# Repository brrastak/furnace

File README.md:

# Furnace for glass fusing

Glass fusing - joining of the pieces of glass. Glass isn't really melted, but is softer than in the normal condition. Planned furnace maximum temperature - 900 °C. Unfortunetely, the project was cancelled due to political reasons. I just want to close my gestalt and finish at least PCBs and firmware.

TODO: more detailed description.

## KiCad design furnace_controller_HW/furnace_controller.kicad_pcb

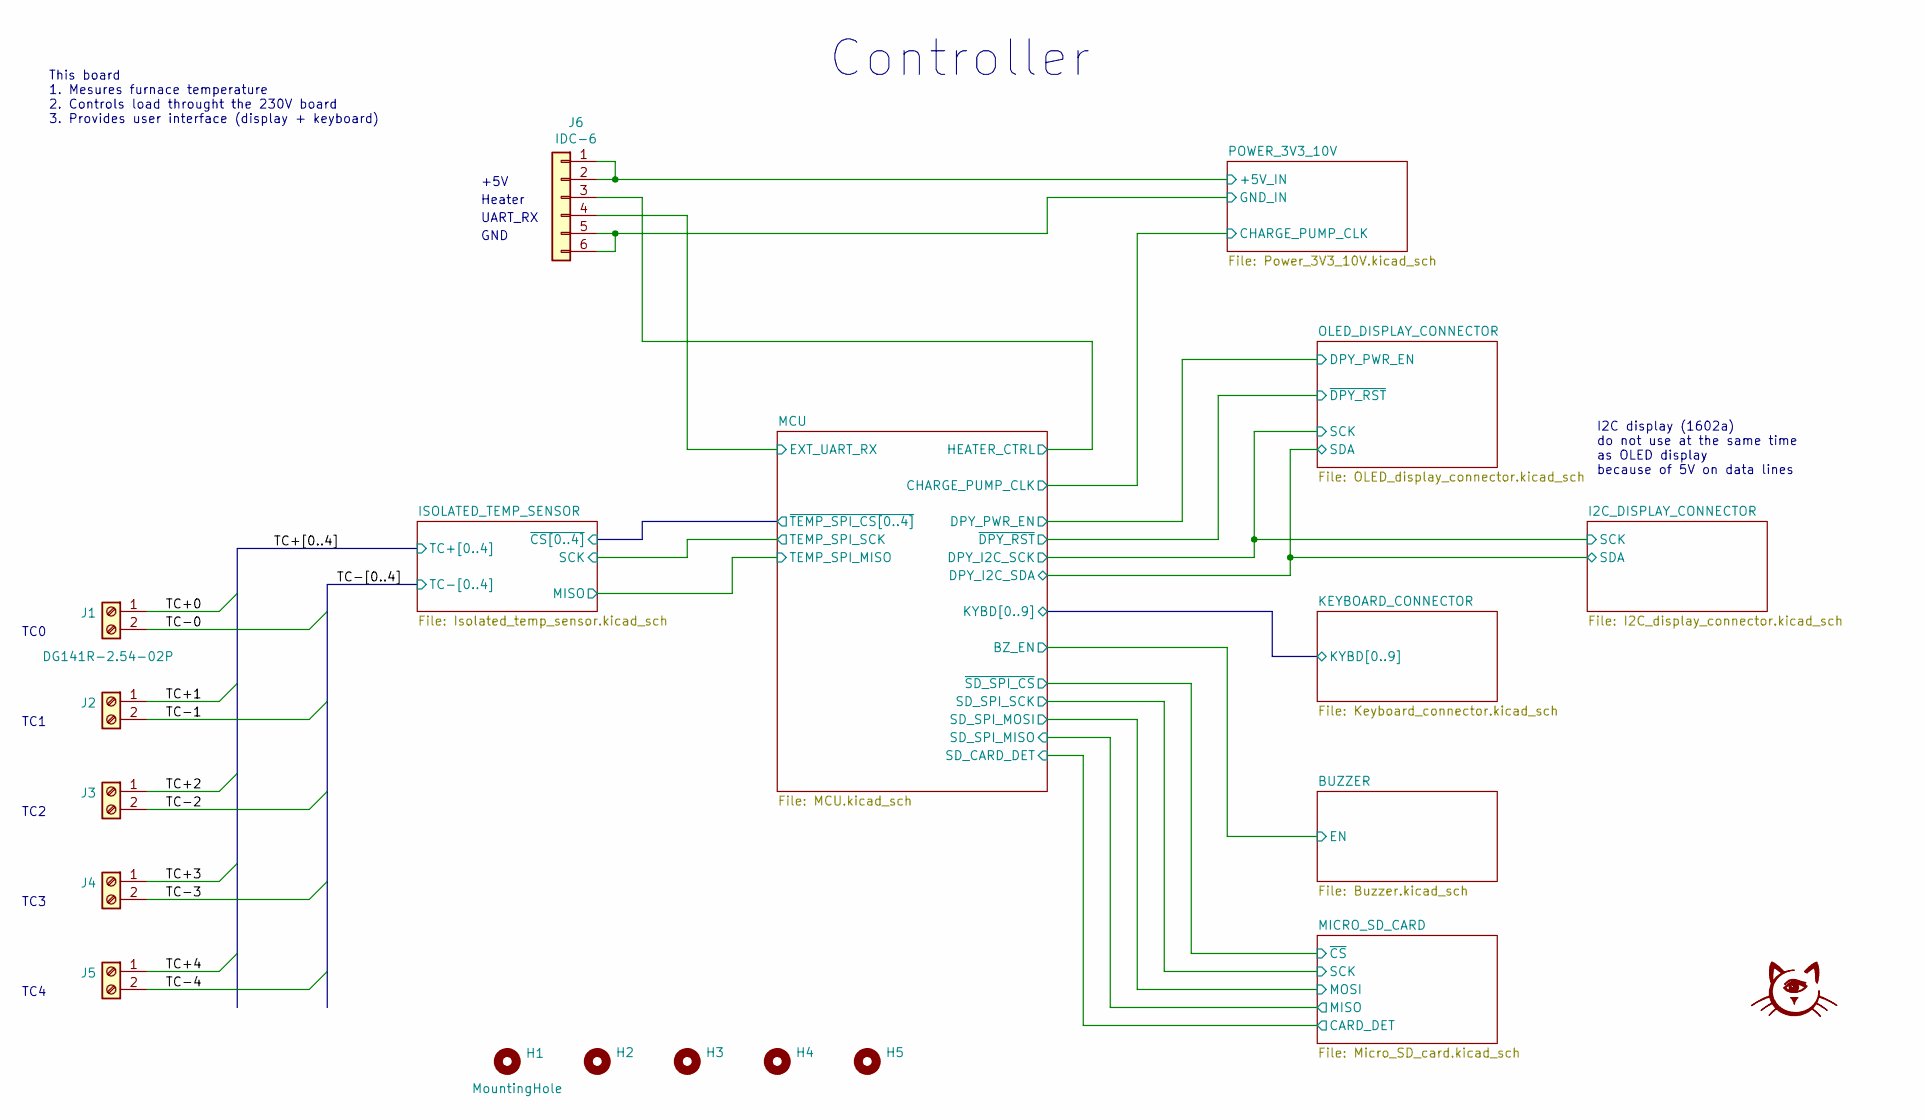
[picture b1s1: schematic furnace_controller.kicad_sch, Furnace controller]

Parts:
G1: LOGO; stamp
H1, H2, H3, H4, H5: MountingHole; hole_D3.5mm
J1, J2, J3, J4, J5: DG141R-2.54-02P
J6: IDC-6; IDC-Header_2x03_P2.54mm_Vertical

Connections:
/MCU/EXT_UART_RX: J6.4; also elsewhere on the board
/MCU/HEATER_CTRL: J6.3; also elsewhere on the board
/POWER_3V3_10V/+5V_IN: J6.1, J6.2; also elsewhere on the board
/TC+0: J1.1; also elsewhere on the board
/TC+1: J2.1; also elsewhere on the board
/TC+2: J3.1; also elsewhere on the board
/TC+3: J4.1; also elsewhere on the board
/TC+4: J5.1; also elsewhere on the board
/TC-0: J1.2; also elsewhere on the board
/TC-1: J2.2; also elsewhere on the board
/TC-2: J3.2; also elsewhere on the board
/TC-3: J4.2; also elsewhere on the board
/TC-4: J5.2; also elsewhere on the board
GND: J6.5, J6.6; also elsewhere on the board

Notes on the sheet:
Controller
TC0
UART_RX
GND
+5V
I2C display (1602a) do not use at the same time as OLED display because of 5V on data lines
TC2
TC1
TC4
TC3
This board 1. Mesures furnace temperature 2. Controls load throught the 230V board 3. Provides user interface (display + keyboard)
Heater

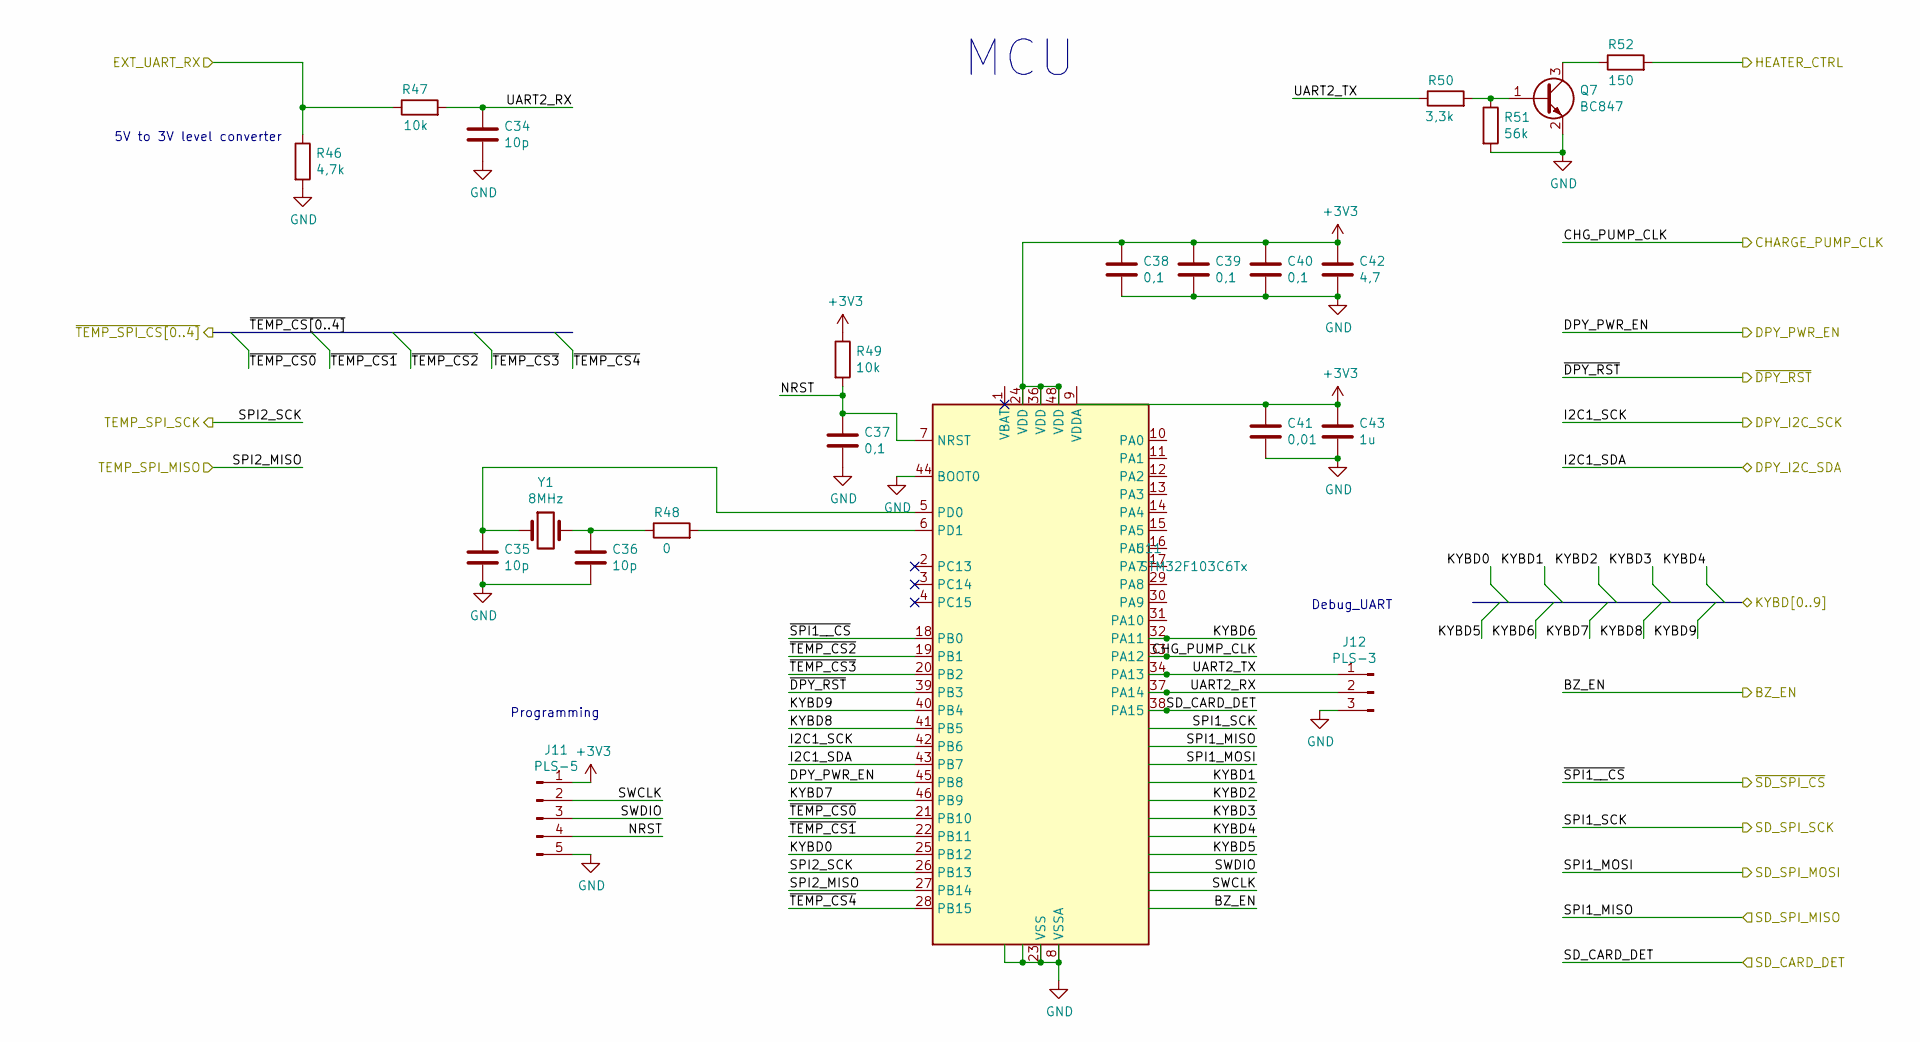
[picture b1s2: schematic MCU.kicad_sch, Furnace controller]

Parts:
C34, C35, C36: 10p; C_0603_1608Metric_Pad1.08x0.95mm_HandSolder
C37, C38, C39, C40: 0,1; C_0603_1608Metric_Pad1.08x0.95mm_HandSolder
C41: 0,01; C_0603_1608Metric_Pad1.08x0.95mm_HandSolder
C42: 4,7; C_1206_3216Metric_Pad1.33x1.80mm_HandSolder
C43: 1u; C_0603_1608Metric_Pad1.08x0.95mm_HandSolder
J11: PLS-5; PinHeader_1x05_P2.54mm_Vertical
J12: PLS-3; PinHeader_1x03_P2.54mm_Vertical
Q7: BC847; SOT-23
R46: 4,7k; R_0603_1608Metric_Pad0.98x0.95mm_HandSolder
R47, R49: 10k; R_0603_1608Metric_Pad0.98x0.95mm_HandSolder
R48: 0; R_0603_1608Metric_Pad0.98x0.95mm_HandSolder
R50: 3,3k; R_0603_1608Metric_Pad0.98x0.95mm_HandSolder
R51: 56k; R_0603_1608Metric_Pad0.98x0.95mm_HandSolder
R52: 150; R_0603_1608Metric_Pad0.98x0.95mm_HandSolder
U11: STM32F103C6Tx; LQFP-48_7x7mm_P0.5mm
Y1: 8MHz; Crystal_SMD_HC49-SD

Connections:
+3V3: C38.1, C39.1, C40.1, C41.1, C42.1, C43.1, J11.1, R49.1, U11.9 (VDDA), U11.24 (VDD), U11.36 (VDD), U11.48 (VDD); also elsewhere on the board
/ISOLATED_TEMP_SENSOR/MISO: U11.27 (PB14); also elsewhere on the board
/ISOLATED_TEMP_SENSOR/SCK: U11.26 (PB13); also elsewhere on the board
/ISOLATED_TEMP_SENSOR/~CS0: U11.21 (PB10); also elsewhere on the board
/ISOLATED_TEMP_SENSOR/~CS1: U11.22 (PB11); also elsewhere on the board
/ISOLATED_TEMP_SENSOR/~CS2: U11.19 (PB1); also elsewhere on the board
/ISOLATED_TEMP_SENSOR/~CS3: U11.20 (PB2); also elsewhere on the board
/ISOLATED_TEMP_SENSOR/~CS4: U11.28 (PB15); also elsewhere on the board
/KEYBOARD_CONNECTOR/KYBD0: U11.25 (PB12); also elsewhere on the board
/KEYBOARD_CONNECTOR/KYBD1: U11.29 (PA8); also elsewhere on the board
/KEYBOARD_CONNECTOR/KYBD2: U11.30 (PA9); also elsewhere on the board
/KEYBOARD_CONNECTOR/KYBD3: U11.31 (PA10); also elsewhere on the board
/KEYBOARD_CONNECTOR/KYBD4: U11.32 (PA11); also elsewhere on the board
/KEYBOARD_CONNECTOR/KYBD5: U11.33 (PA12); also elsewhere on the board
/KEYBOARD_CONNECTOR/KYBD6: U11.10 (PA0); also elsewhere on the board
/KEYBOARD_CONNECTOR/KYBD7: U11.46 (PB9); also elsewhere on the board
/KEYBOARD_CONNECTOR/KYBD8: U11.41 (PB5); also elsewhere on the board
/KEYBOARD_CONNECTOR/KYBD9: U11.40 (PB4); also elsewhere on the board
/MCU/BZ_EN: U11.38 (PA15); also elsewhere on the board
/MCU/CHARGE_PUMP_CLK: U11.11 (PA1); also elsewhere on the board
/MCU/DPY_I2C_SCK: U11.42 (PB6); also elsewhere on the board
/MCU/DPY_I2C_SDA: U11.43 (PB7); also elsewhere on the board
/MCU/DPY_PWR_EN: U11.45 (PB8); also elsewhere on the board
/MCU/EXT_UART_RX: R46.1, R47.1; also elsewhere on the board
/MCU/HEATER_CTRL: R52.2; also elsewhere on the board
/MCU/NRST: C37.1, J11.4, R49.2, U11.7 (NRST)
/MCU/~DPY_RST: U11.39 (PB3); also elsewhere on the board
/MICRO_SD_CARD/CARD_DET: U11.14 (PA4); also elsewhere on the board
/MICRO_SD_CARD/MISO: U11.16 (PA6); also elsewhere on the board
/MICRO_SD_CARD/MOSI: U11.17 (PA7); also elsewhere on the board
/MICRO_SD_CARD/SCK: U11.15 (PA5); also elsewhere on the board
/MICRO_SD_CARD/~CS: U11.18 (PB0); also elsewhere on the board
GND: C34.2, C35.2, C36.2, C37.2, C38.2, C39.2, C40.2, C41.2, C42.2, C43.2, J11.5, J12.3, Q7.2 (E), R46.2, R51.2, U11.8 (VSSA), U11.23 (VSS), U11.35 (VSS), U11.44 (BOOT0), U11.47 (VSS); also elsewhere on the board
unnamed: C35.1, U11.5 (PD0), Y1.1
unnamed: C36.1, R48.1, Y1.2
unnamed: Q7.1 (B), R50.2, R51.1
unnamed: Q7.3 (C), R52.1
unnamed: R48.2, U11.6 (PD1)

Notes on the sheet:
Debug_UART
Programming
MCU
5V to 3V level converter

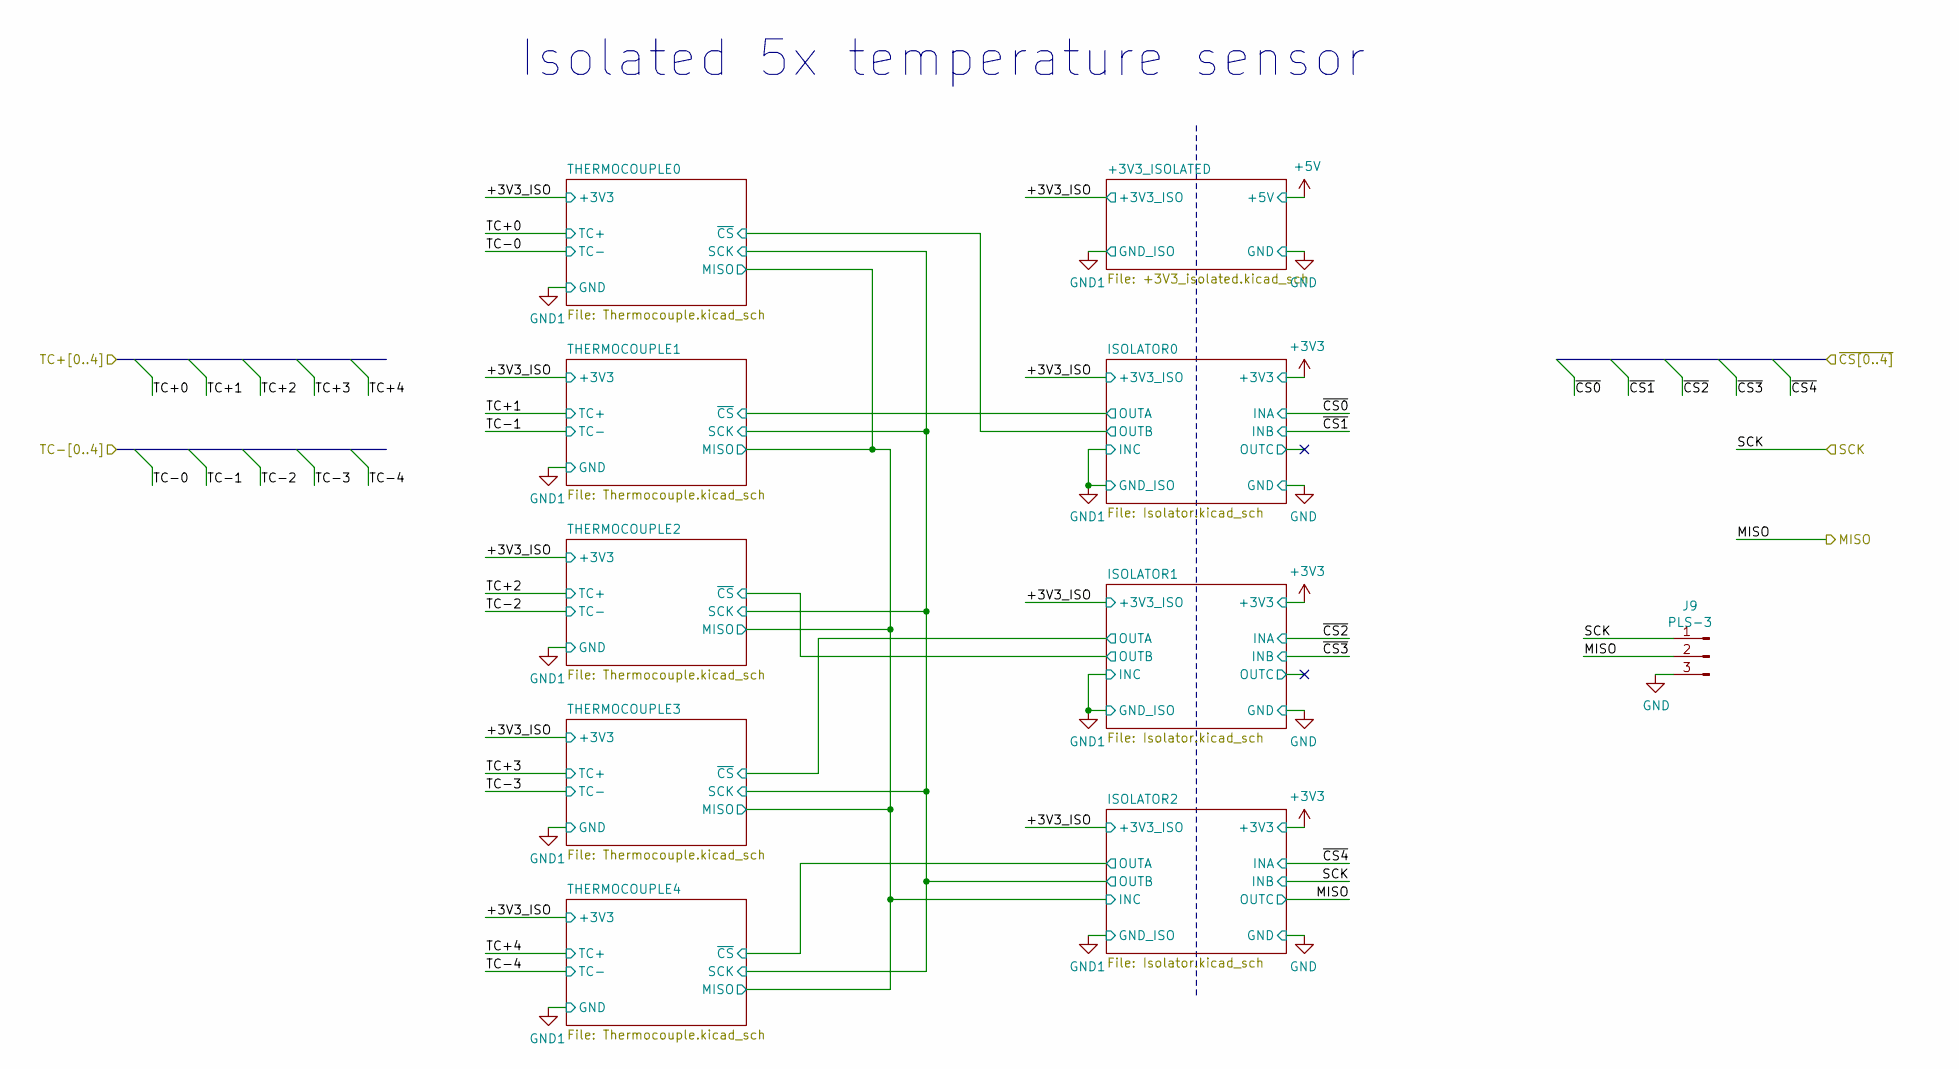
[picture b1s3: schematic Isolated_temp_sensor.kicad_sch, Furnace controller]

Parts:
J9: PLS-3; PinHeader_1x03_P2.54mm_Vertical

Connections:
/ISOLATED_TEMP_SENSOR/MISO: J9.2; also elsewhere on the board
/ISOLATED_TEMP_SENSOR/SCK: J9.1; also elsewhere on the board
GND: J9.3; also elsewhere on the board

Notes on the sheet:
Isolated 5x temperature sensor

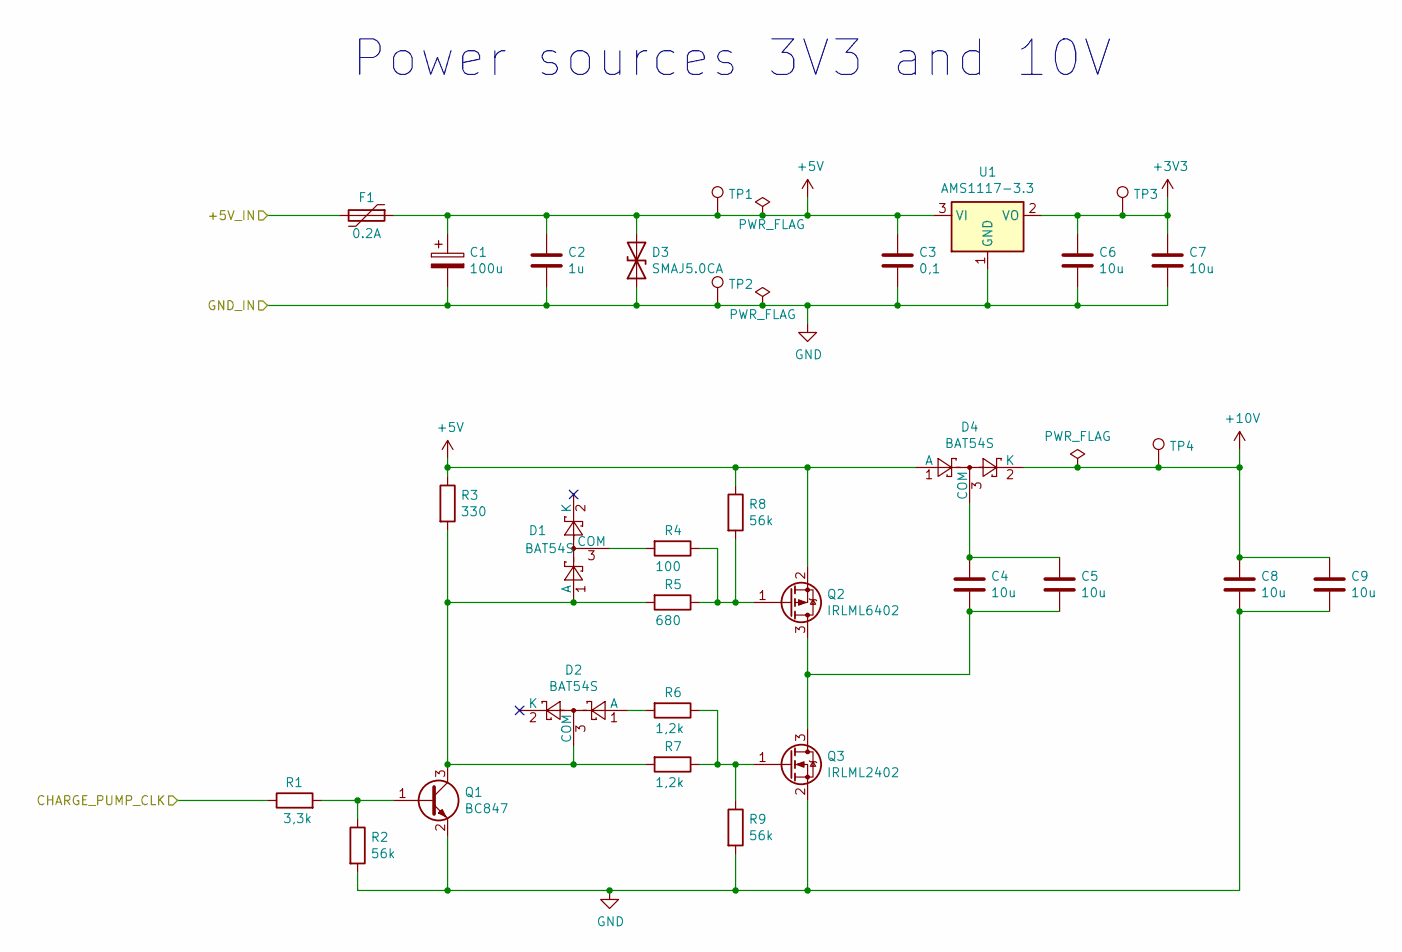
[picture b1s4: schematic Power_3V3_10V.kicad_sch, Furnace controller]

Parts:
C1: 100u; CP_Radial_D5.0mm_P2.00mm
C2: 1u; C_0603_1608Metric_Pad1.08x0.95mm_HandSolder
C3: 0,1; C_0603_1608Metric_Pad1.08x0.95mm_HandSolder
C4, C5, C6, C7, C8, C9: 10u; C_1206_3216Metric_Pad1.33x1.80mm_HandSolder
D1, D2, D4: BAT54S; SOT-23
D3: SMAJ5.0CA; D_SMB_Handsoldering
F1: 0.2A; Fuse_1206_3216Metric_Pad1.42x1.75mm_HandSolder
Q1: BC847; SOT-23
Q2: IRLML6402; SOT-23
Q3: IRLML2402; SOT-23
R1: 3,3k; R_0603_1608Metric_Pad0.98x0.95mm_HandSolder
R2, R8, R9: 56k; R_0603_1608Metric_Pad0.98x0.95mm_HandSolder
R3: 330; R_0603_1608Metric_Pad0.98x0.95mm_HandSolder
R4: 100; R_0603_1608Metric_Pad0.98x0.95mm_HandSolder
R5: 680; R_0603_1608Metric_Pad0.98x0.95mm_HandSolder
R6, R7: 1,2k; R_0603_1608Metric_Pad0.98x0.95mm_HandSolder
TP1, TP2, TP3, TP4: TestPoint; TP
U1: AMS1117-3.3; SOT-223-3_TabPin2

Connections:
+3V3: C6.1, C7.1, TP3.1, U1.2 (VO); also elsewhere on the board
+5V: C1.1, C2.1, C3.1, D3.2 (A2), D4.1 (A), F1.1, Q2.2 (S), R3.1, R8.1, TP1.1, U1.3 (VI); also elsewhere on the board
+10V: C8.1, C9.1, D4.2 (K), TP4.1; also elsewhere on the board
/MCU/CHARGE_PUMP_CLK: R1.1; also elsewhere on the board
/POWER_3V3_10V/+5V_IN: F1.2; also elsewhere on the board
GND: C1.2, C2.2, C3.2, C6.2, C7.2, C8.2, C9.2, D3.1 (A1), Q1.2 (E), Q3.2 (S), R2.2, R9.2, TP2.1, U1.1 (GND); also elsewhere on the board
unnamed: C4.1, C5.1, D4.3 (COM)
unnamed: C4.2, C5.2, Q2.3 (D), Q3.3 (D)
unnamed: D1.1 (A), D2.3 (COM), Q1.3 (C), R3.2, R5.2, R7.2
unnamed: D1.3 (COM), R4.2
unnamed: D2.1 (A), R6.2
unnamed: Q1.1 (B), R1.2, R2.1
unnamed: Q2.1 (G), R4.1, R5.1, R8.2
unnamed: Q3.1 (G), R6.1, R7.1, R9.1

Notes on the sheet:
Power sources 3V3 and 10V

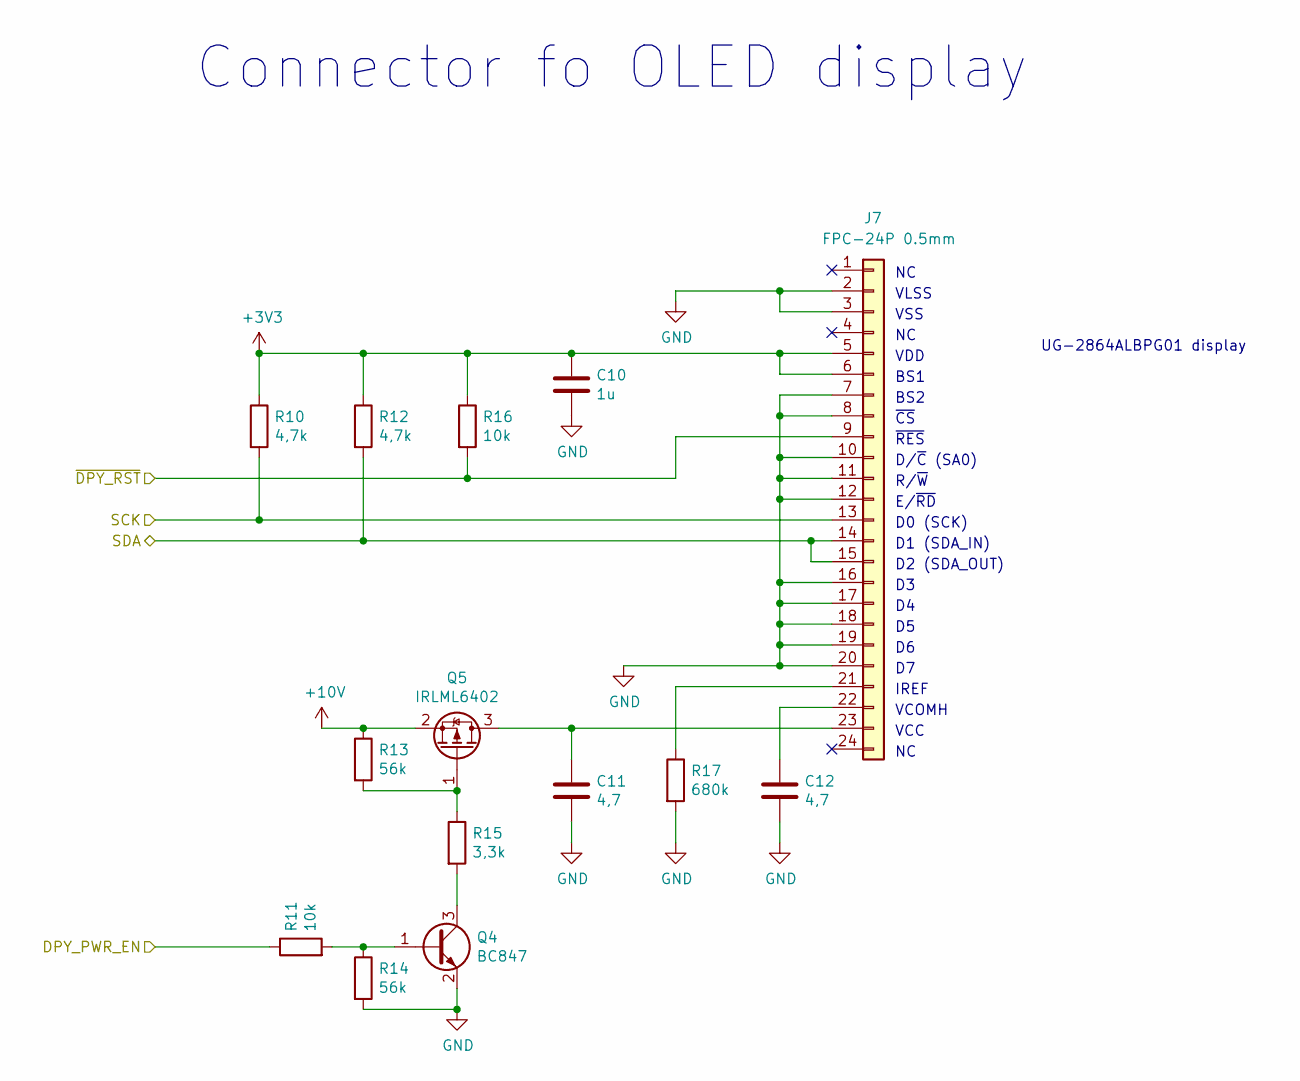
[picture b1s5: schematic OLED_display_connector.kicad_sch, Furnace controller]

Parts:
C10: 1u; C_0603_1608Metric_Pad1.08x0.95mm_HandSolder
C11, C12: 4,7; C_1206_3216Metric_Pad1.33x1.80mm_HandSolder
J7: FPC-24P 0.5mm; Hirose_FH12-24S-0.5SH_1x24-1MP_P0.50mm_Horizontal
Q4: BC847; SOT-23
Q5: IRLML6402; SOT-23
R10, R12: 4,7k; R_0603_1608Metric_Pad0.98x0.95mm_HandSolder
R11, R16: 10k; R_0603_1608Metric_Pad0.98x0.95mm_HandSolder
R13, R14: 56k; R_0603_1608Metric_Pad0.98x0.95mm_HandSolder
R15: 3,3k; R_0603_1608Metric_Pad0.98x0.95mm_HandSolder
R17: 680k; R_0603_1608Metric_Pad0.98x0.95mm_HandSolder

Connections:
+3V3: C10.1, J7.5, J7.6, R10.1, R12.1, R16.1; also elsewhere on the board
+10V: Q5.2 (S), R13.1; also elsewhere on the board
/MCU/DPY_I2C_SCK: J7.13, R10.2; also elsewhere on the board
/MCU/DPY_I2C_SDA: J7.14, J7.15, R12.2; also elsewhere on the board
/MCU/DPY_PWR_EN: R11.1; also elsewhere on the board
/MCU/~DPY_RST: J7.9, R16.2; also elsewhere on the board
GND: C10.2, C11.2, C12.2, J7.2, J7.3, J7.7, J7.8, J7.10, J7.11, J7.12, J7.16, J7.17, J7.18, J7.19, J7.20, Q4.2 (E), R14.2, R17.2; also elsewhere on the board
unnamed: C11.1, J7.23, Q5.3 (D)
unnamed: C12.1, J7.22
unnamed: J7.21, R17.1
unnamed: Q4.1 (B), R11.2, R14.1
unnamed: Q4.3 (C), R15.2
unnamed: Q5.1 (G), R13.2, R15.1

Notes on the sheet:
BS1
BS2
VLSS
UG-2864ALBPG01 display
R/~{W}
~{RES}
VSS
Connector fo OLED display
VCOMH
E/~{RD}
D/~{C} (SA0)
D1 (SDA_IN)
VCC
IREF
~{CS}
D0 (SCK)
D2 (SDA_OUT)
VDD

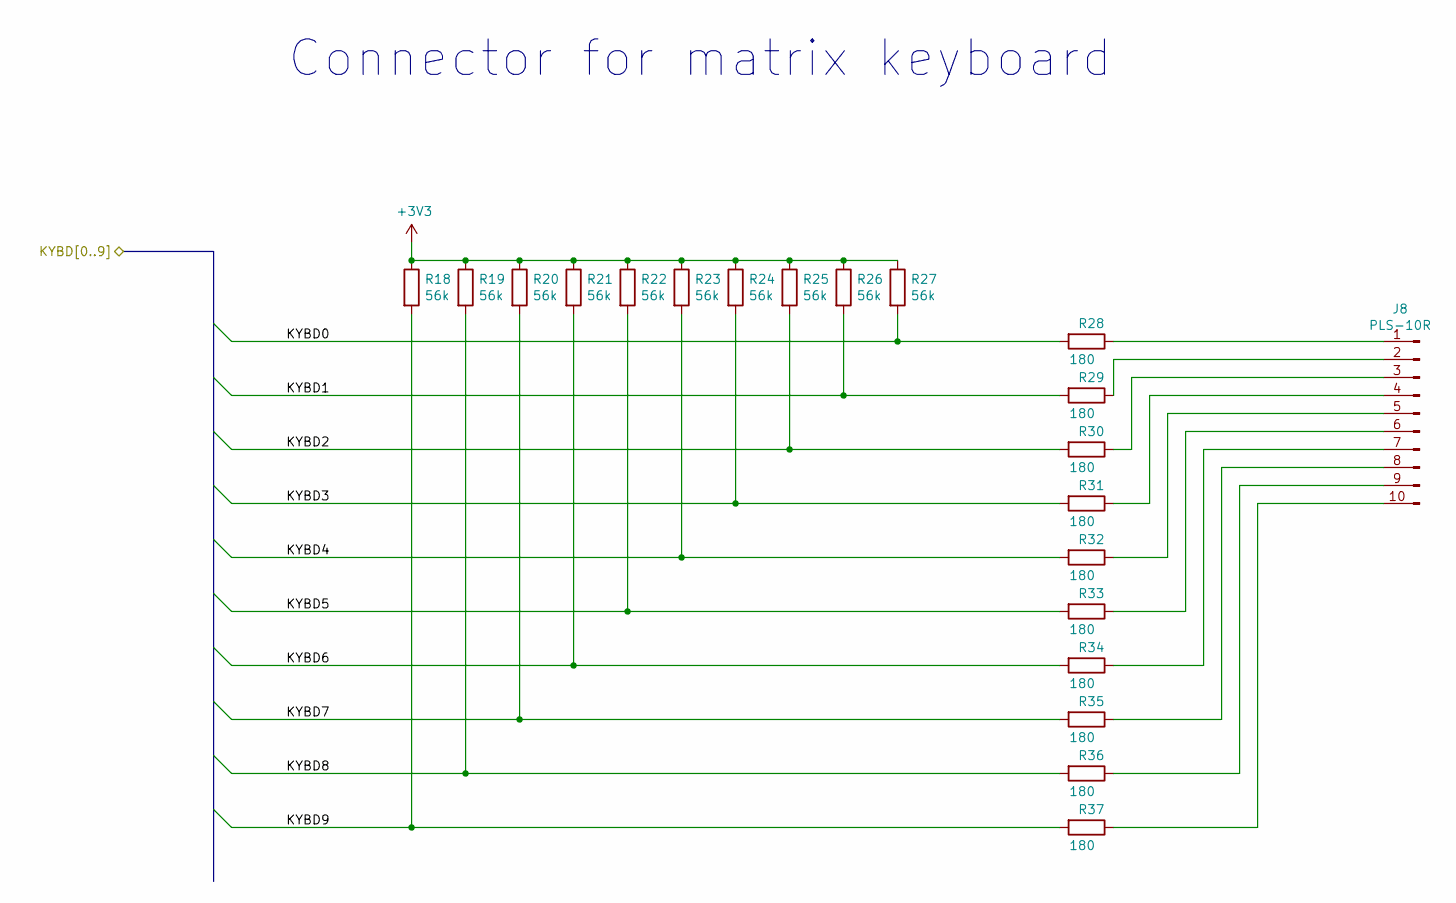
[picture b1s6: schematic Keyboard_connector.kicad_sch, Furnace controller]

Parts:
J8: PLS-10R; PinHeader_1x10_P2.54mm_Vertical
R18, R19, R20, R21, R22, R23, R24, R25, R26, R27: 56k; R_0603_1608Metric_Pad0.98x0.95mm_HandSolder
R28, R29, R30, R31, R32, R33, R34, R35, R36, R37: 180; R_0603_1608Metric_Pad0.98x0.95mm_HandSolder

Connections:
+3V3: R18.1, R19.1, R20.1, R21.1, R22.1, R23.1, R24.1, R25.1, R26.1, R27.1; also elsewhere on the board
/KEYBOARD_CONNECTOR/KYBD0: R27.2, R28.2; also elsewhere on the board
/KEYBOARD_CONNECTOR/KYBD1: R26.2, R29.2; also elsewhere on the board
/KEYBOARD_CONNECTOR/KYBD2: R25.2, R30.2; also elsewhere on the board
/KEYBOARD_CONNECTOR/KYBD3: R24.2, R31.2; also elsewhere on the board
/KEYBOARD_CONNECTOR/KYBD4: R23.2, R32.2; also elsewhere on the board
/KEYBOARD_CONNECTOR/KYBD5: R22.2, R33.2; also elsewhere on the board
/KEYBOARD_CONNECTOR/KYBD6: R21.2, R34.2; also elsewhere on the board
/KEYBOARD_CONNECTOR/KYBD7: R20.2, R35.2; also elsewhere on the board
/KEYBOARD_CONNECTOR/KYBD8: R19.2, R36.2; also elsewhere on the board
/KEYBOARD_CONNECTOR/KYBD9: R18.2, R37.2; also elsewhere on the board
unnamed: J8.1, R28.1
unnamed: J8.2, R29.1
unnamed: J8.3, R30.1
unnamed: J8.4, R31.1
unnamed: J8.5, R32.1
unnamed: J8.6, R33.1
unnamed: J8.7, R34.1
unnamed: J8.8, R35.1
unnamed: J8.9, R36.1
unnamed: J8.10, R37.1

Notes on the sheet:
Connector for matrix keyboard

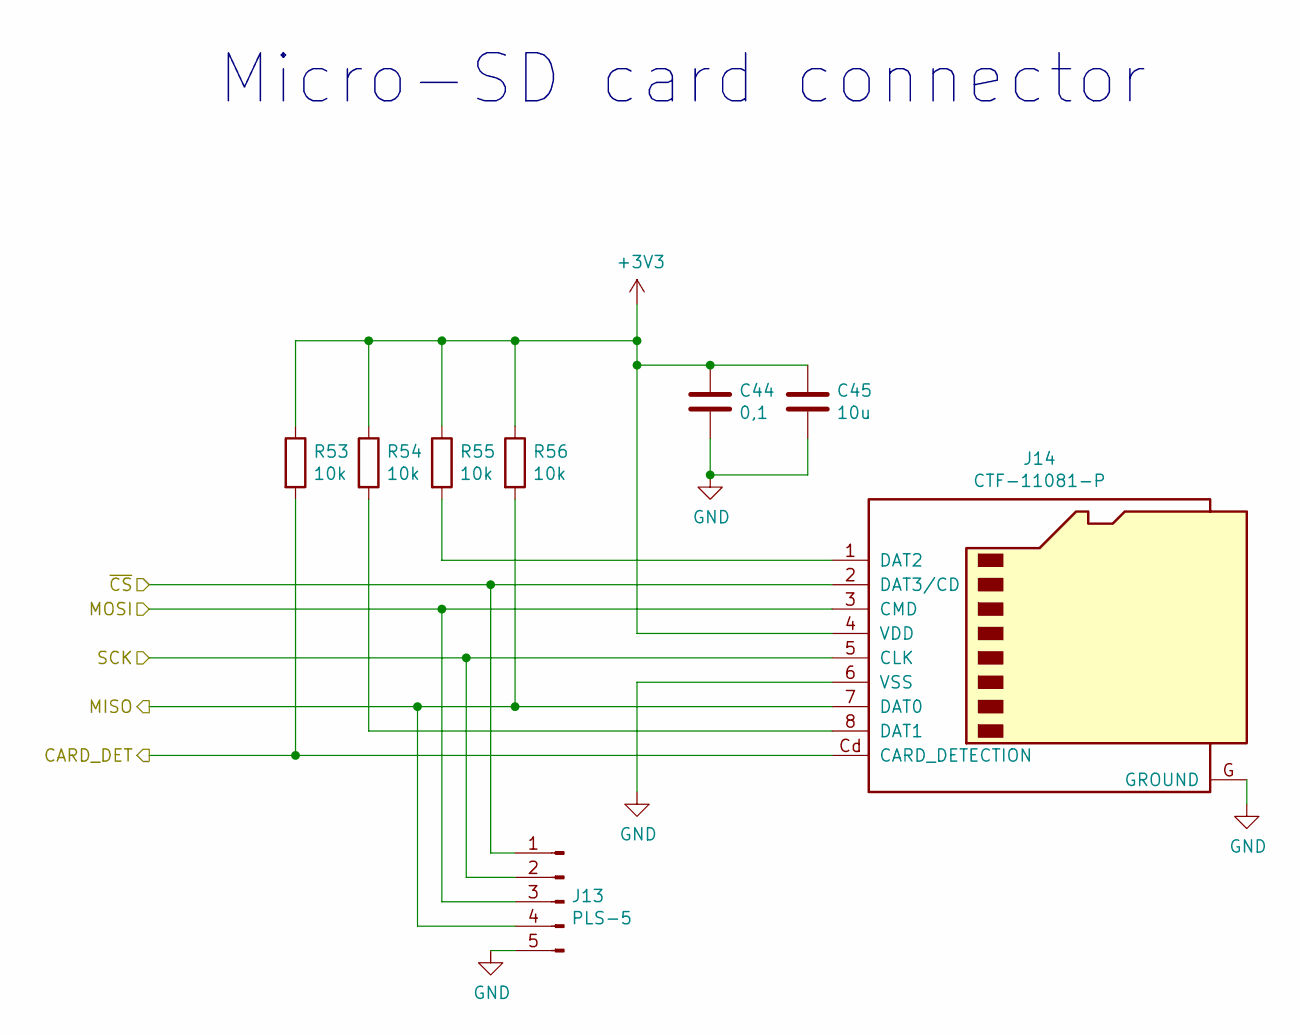
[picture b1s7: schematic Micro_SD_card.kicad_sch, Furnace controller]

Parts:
C44: 0,1; C_0603_1608Metric_Pad1.08x0.95mm_HandSolder
C45: 10u; C_1206_3216Metric_Pad1.33x1.80mm_HandSolder
J13: PLS-5; PinHeader_1x05_P2.54mm_Vertical
J14: CTF-11081-P
R53, R54, R55, R56: 10k; R_0603_1608Metric_Pad0.98x0.95mm_HandSolder

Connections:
+3V3: C44.1, C45.1, J14.4 (VDD), R53.1, R54.1, R55.1, R56.1; also elsewhere on the board
/MICRO_SD_CARD/CARD_DET: J14.Cd (CARD_DETECTION), R53.2; also elsewhere on the board
/MICRO_SD_CARD/MISO: J13.4, J14.7 (DAT0), R56.2; also elsewhere on the board
/MICRO_SD_CARD/MOSI: J13.3, J14.3 (CMD); also elsewhere on the board
/MICRO_SD_CARD/SCK: J13.2, J14.5 (CLK); also elsewhere on the board
/MICRO_SD_CARD/~CS: J13.1, J14.2 (DAT3/CD); also elsewhere on the board
GND: C44.2, C45.2, J13.5, J14.6 (VSS), J14.G (GROUND); also elsewhere on the board
unnamed: J14.1 (DAT2), R55.2
unnamed: J14.8 (DAT1), R54.2

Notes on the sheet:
Micro-SD card connector

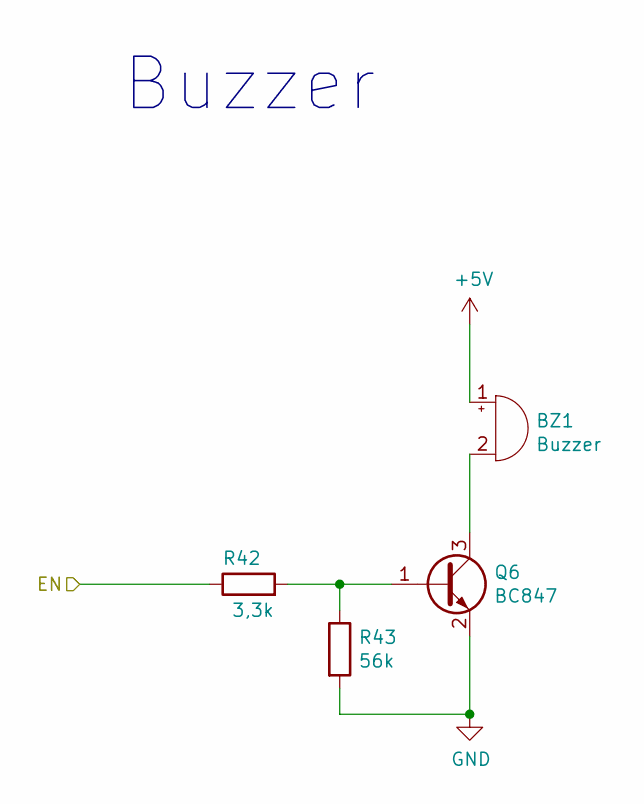
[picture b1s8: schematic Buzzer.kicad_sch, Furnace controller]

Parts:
BZ1: Buzzer; Buzzer_12x9.5RM7.6
Q6: BC847; SOT-23
R42: 3,3k; R_0603_1608Metric_Pad0.98x0.95mm_HandSolder
R43: 56k; R_0603_1608Metric_Pad0.98x0.95mm_HandSolder

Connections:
+5V: BZ1.1 (+); also elsewhere on the board
/MCU/BZ_EN: R42.1; also elsewhere on the board
GND: Q6.2 (E), R43.2; also elsewhere on the board
unnamed: BZ1.2 (-), Q6.3 (C)
unnamed: Q6.1 (B), R42.2, R43.1

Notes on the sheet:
Buzzer

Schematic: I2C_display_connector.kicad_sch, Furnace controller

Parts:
J10: PLS-4R; PinHeader_1x04_P2.54mm_Horizontal
JP1: Jumper_NC_Dual; PinHeader_1x03_P2.54mm_Vertical
R44, R45: 4,7k; R_0603_1608Metric_Pad0.98x0.95mm_HandSolder

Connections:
+3V3: JP1.3; also elsewhere on the board
+5V: JP1.1; also elsewhere on the board
/MCU/DPY_I2C_SCK: J10.1, R44.2; also elsewhere on the board
/MCU/DPY_I2C_SDA: J10.2, R45.2; also elsewhere on the board
GND: J10.4; also elsewhere on the board
unnamed: J10.3, JP1.2, R44.1, R45.1

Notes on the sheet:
I2C display connector for OLED or LCD display

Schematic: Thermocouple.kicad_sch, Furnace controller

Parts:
C13: 0,01; C_0603_1608Metric_Pad1.08x0.95mm_HandSolder
C14: 0,1; C_0603_1608Metric_Pad1.08x0.95mm_HandSolder
U2: MAX31855EASA; SOIC-8_3.9x4.9mm_P1.27mm

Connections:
/ISOLATED_TEMP_SENSOR/+3V3_ISO: C14.1, U2.4 (V_{CC}); also elsewhere on the board
/ISOLATED_TEMP_SENSOR/ISOLATOR0/OUTB: U2.6 (~CS); also elsewhere on the board
/ISOLATED_TEMP_SENSOR/ISOLATOR2/INC: U2.7 (SO); also elsewhere on the board
/ISOLATED_TEMP_SENSOR/ISOLATOR2/OUTB: U2.5 (SCK); also elsewhere on the board
/TC+0: C13.1, U2.3 (T+); also elsewhere on the board
/TC-0: C13.2, U2.2 (T-); also elsewhere on the board
GND1: C14.2, U2.1 (GND); also elsewhere on the board

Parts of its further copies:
C22, C24, C26, C28: 0,01; C_0603_1608Metric_Pad1.08x0.95mm_HandSolder
C23, C25, C27, C29: 0,1; C_0603_1608Metric_Pad1.08x0.95mm_HandSolder
U5, U6, U7, U8: MAX31855EASA; SOIC-8_3.9x4.9mm_P1.27mm

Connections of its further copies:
/ISOLATED_TEMP_SENSOR/+3V3_ISO: C23.1, C25.1, C27.1, C29.1, U5.4 (V_{CC}), U6.4 (V_{CC}), U7.4 (V_{CC}), U8.4 (V_{CC}); also elsewhere on the board
/ISOLATED_TEMP_SENSOR/ISOLATOR0/OUTA: U5.6 (~CS); also elsewhere on the board
/ISOLATED_TEMP_SENSOR/ISOLATOR1/OUTA: U7.6 (~CS); also elsewhere on the board
/ISOLATED_TEMP_SENSOR/ISOLATOR1/OUTB: U6.6 (~CS); also elsewhere on the board
/ISOLATED_TEMP_SENSOR/ISOLATOR2/INC: U5.7 (SO), U6.7 (SO), U7.7 (SO), U8.7 (SO); also elsewhere on the board
/ISOLATED_TEMP_SENSOR/ISOLATOR2/OUTA: U8.6 (~CS); also elsewhere on the board
/ISOLATED_TEMP_SENSOR/ISOLATOR2/OUTB: U5.5 (SCK), U6.5 (SCK), U7.5 (SCK), U8.5 (SCK); also elsewhere on the board
/TC+1: C22.1, U5.3 (T+); also elsewhere on the board
/TC+2: C24.1, U6.3 (T+); also elsewhere on the board
/TC+3: C26.1, U7.3 (T+); also elsewhere on the board
/TC+4: C28.1, U8.3 (T+); also elsewhere on the board
/TC-1: C22.2, U5.2 (T-); also elsewhere on the board
/TC-2: C24.2, U6.2 (T-); also elsewhere on the board
/TC-3: C26.2, U7.2 (T-); also elsewhere on the board
/TC-4: C28.2, U8.2 (T-); also elsewhere on the board
GND1: C23.2, C25.2, C27.2, C29.2, U5.1 (GND), U6.1 (GND), U7.1 (GND), U8.1 (GND); also elsewhere on the board

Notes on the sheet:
Thermocouple sensor

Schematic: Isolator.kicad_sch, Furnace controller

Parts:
C15, C16: 0,1; C_0603_1608Metric_Pad1.08x0.95mm_HandSolder
U3: ADuM1301; SOIC-16W_7.5x10.3mm_P1.27mm

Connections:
+3V3: C16.1, U3.1 (VDD1), U3.7 (VE1); also elsewhere on the board
/ISOLATED_TEMP_SENSOR/+3V3_ISO: C15.1, U3.10 (VE2), U3.16 (VDD2); also elsewhere on the board
/ISOLATED_TEMP_SENSOR/ISOLATOR0/OUTA: U3.14 (VOA); also elsewhere on the board
/ISOLATED_TEMP_SENSOR/ISOLATOR0/OUTB: U3.13 (VOB); also elsewhere on the board
/ISOLATED_TEMP_SENSOR/ISOLATOR0/OUTC: U3.5 (VOC)
/ISOLATED_TEMP_SENSOR/~CS0: U3.3 (VIA); also elsewhere on the board
/ISOLATED_TEMP_SENSOR/~CS1: U3.4 (VIB); also elsewhere on the board
GND: C16.2, U3.2 (GND1), U3.8 (GND1); also elsewhere on the board
GND1: C15.2, U3.9 (GND2), U3.12 (VIC), U3.15 (GND2); also elsewhere on the board

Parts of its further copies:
C30, C31, C32, C33: 0,1; C_0603_1608Metric_Pad1.08x0.95mm_HandSolder
U9, U10: ADuM1301; SOIC-16W_7.5x10.3mm_P1.27mm

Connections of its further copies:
+3V3: C31.1, C33.1, U9.1 (VDD1), U9.7 (VE1), U10.1 (VDD1), U10.7 (VE1); also elsewhere on the board
/ISOLATED_TEMP_SENSOR/+3V3_ISO: C30.1, C32.1, U9.10 (VE2), U9.16 (VDD2), U10.10 (VE2), U10.16 (VDD2); also elsewhere on the board
/ISOLATED_TEMP_SENSOR/ISOLATOR1/OUTA: U9.14 (VOA); also elsewhere on the board
/ISOLATED_TEMP_SENSOR/ISOLATOR1/OUTB: U9.13 (VOB); also elsewhere on the board
/ISOLATED_TEMP_SENSOR/ISOLATOR1/OUTC: U9.5 (VOC)
/ISOLATED_TEMP_SENSOR/ISOLATOR2/INC: U10.12 (VIC); also elsewhere on the board
/ISOLATED_TEMP_SENSOR/ISOLATOR2/OUTA: U10.14 (VOA); also elsewhere on the board
/ISOLATED_TEMP_SENSOR/ISOLATOR2/OUTB: U10.13 (VOB); also elsewhere on the board
/ISOLATED_TEMP_SENSOR/MISO: U10.5 (VOC); also elsewhere on the board
/ISOLATED_TEMP_SENSOR/SCK: U10.4 (VIB); also elsewhere on the board
/ISOLATED_TEMP_SENSOR/~CS2: U9.3 (VIA); also elsewhere on the board
/ISOLATED_TEMP_SENSOR/~CS3: U9.4 (VIB); also elsewhere on the board
/ISOLATED_TEMP_SENSOR/~CS4: U10.3 (VIA); also elsewhere on the board
GND: C31.2, C33.2, U9.2 (GND1), U9.8 (GND1), U10.2 (GND1), U10.8 (GND1); also elsewhere on the board
GND1: C30.2, C32.2, U9.9 (GND2), U9.12 (VIC), U9.15 (GND2), U10.9 (GND2), U10.15 (GND2); also elsewhere on the board

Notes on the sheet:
Isolator for thermocouple

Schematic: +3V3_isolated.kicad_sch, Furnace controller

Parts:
C17: 4,7; C_1206_3216Metric_Pad1.33x1.80mm_HandSolder
C18, C20: 10u; C_1206_3216Metric_Pad1.33x1.80mm_HandSolder
C19: 0,1; C_0603_1608Metric_Pad1.08x0.95mm_HandSolder
C21: 1u; C_0603_1608Metric_Pad1.08x0.95mm_HandSolder
FB1: Ferrite_Bead; L_0805_2012Metric_Pad1.05x1.20mm_HandSolder
PS1: B0505S-1WR2; B_S-1WR3; PARTREV 2018.12.05-B/2
R38, R39: 680; R_0603_1608Metric_Pad0.98x0.95mm_HandSolder
R40: 240 1%; R_0603_1608Metric_Pad0.98x0.95mm_HandSolder
R41: 390 1%; R_0603_1608Metric_Pad0.98x0.95mm_HandSolder
TP5, TP6: TestPoint; TP
U4: LM317L_SO8; SOIC-8_3.9x4.9mm_P1.27mm

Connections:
+5V: C17.1, PS1.2 (VIN); also elsewhere on the board
/ISOLATED_TEMP_SENSOR/+3V3_ISO: C21.1, R40.1, TP5.1, U4.2 (VO), U4.3 (VO), U4.6 (VO), U4.7 (VO); also elsewhere on the board
GND: C17.2, PS1.1 (GND); also elsewhere on the board
GND1: C18.2, C19.2, C20.2, C21.2, PS1.3 (0V), R38.2, R39.2, R41.2, TP6.1; also elsewhere on the board
unnamed: C18.1, FB1.2, PS1.4 (+VO)
unnamed: C19.1, FB1.1, R38.1, R39.1, U4.1 (VI)
unnamed: C20.1, R40.2, R41.1, U4.4 (ADJ)

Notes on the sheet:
Isolated +3V3 power source

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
